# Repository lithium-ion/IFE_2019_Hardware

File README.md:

View this project on [CADLAB.io](https://cadlab.io/project/1221). 

# IFE_2019_Hardware
Hardware System - Eagle Files + Spice Code

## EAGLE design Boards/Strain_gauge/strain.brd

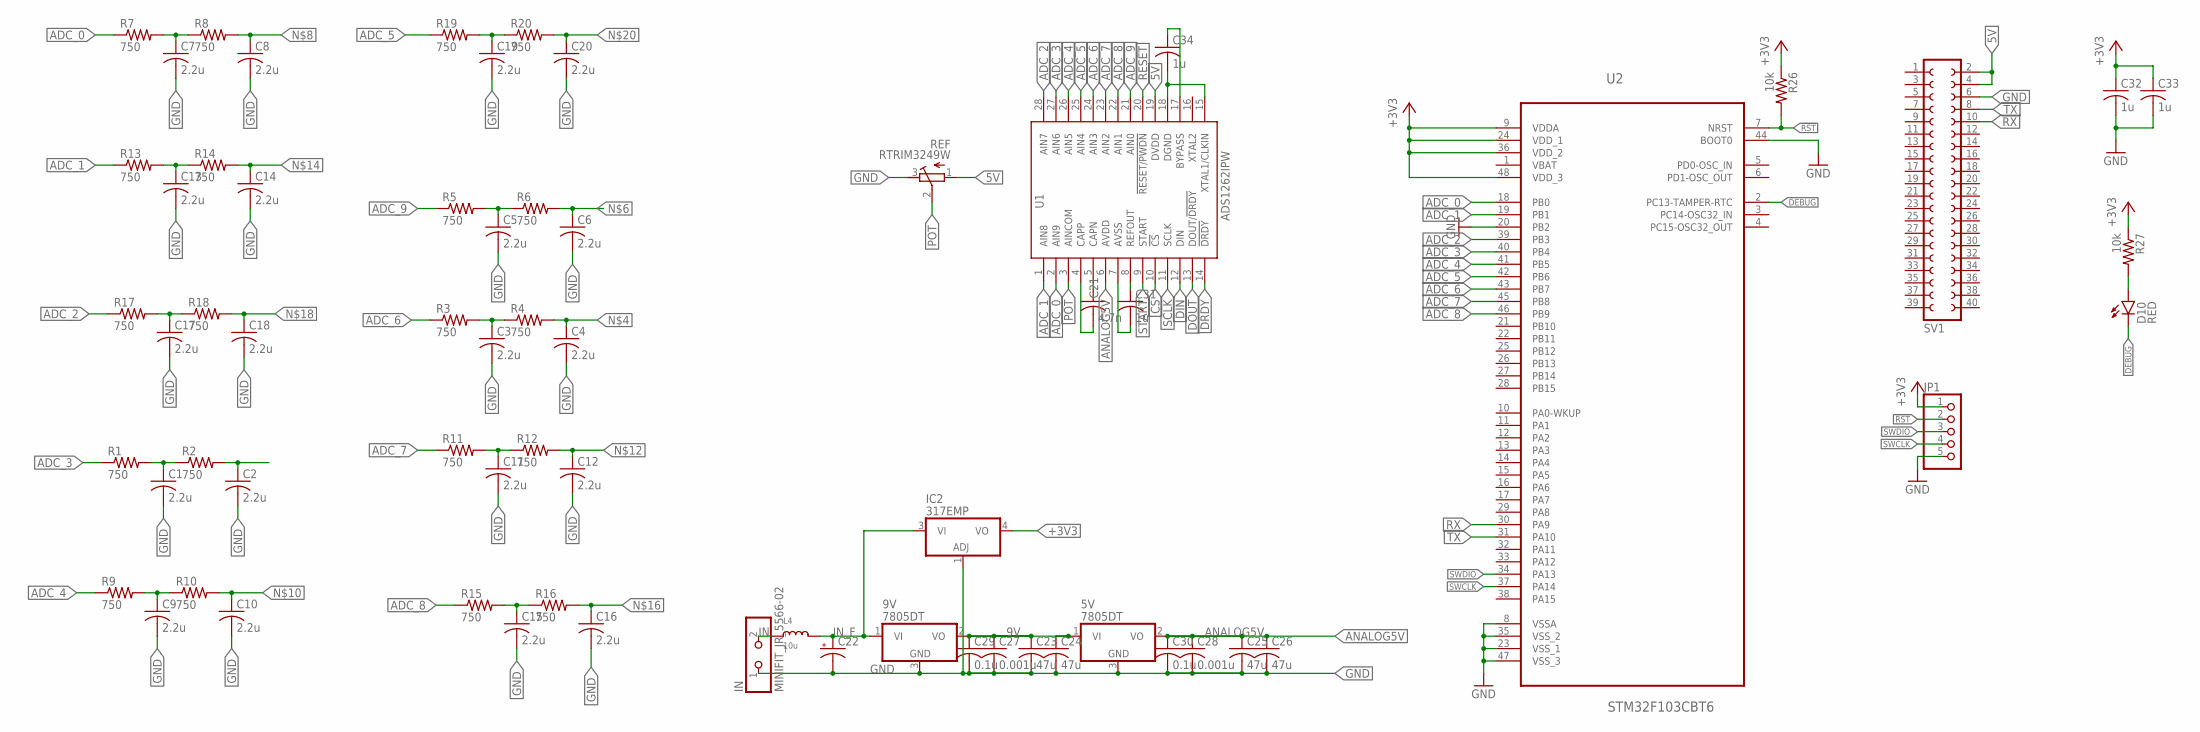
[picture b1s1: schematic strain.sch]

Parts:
5V, 9V: 7805DT; TO252
C1, C2, C3, C4, C5, C6, C7, C8, C9, C10, C11, C12, C13, C14, C15, C16, C17, C18, C19, C20: 2.2u; C0805
C21: 4.7n; C0805
C22: CPOL-USE5-10.5; E5-10,5
C23, C24, C25, C26: 47u; C1210
C27, C28: 0.001u; C0603
C29, C30: 0.1u; C0603
C31, C32, C33, C34: 1u; C0805
D10: RED; LED-0603
IC2: 317EMP; SOT223
IN: MINIFIT_JR_5566-02
JP1: PINHD-1X5; 1X05
L4: 10u; INDUCTOR_5X5MM_NR5040_NOTHERMALS
R1, R2, R3, R4, R5, R6, R7, R8, R9, R10, R11, R12, R13, R14, R15, R16, R17, R18, R19, R20: 750; R0805
R26, R27: 10k; R0603
REF: RTRIM3249W; RTRIM3299W
SV1: FE20-2
U1: ADS1262IPW; TSSOP28
U2: STM32F103CBT6; QFP50P900X900X160-48N

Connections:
5V: REF.1 (A), SV1.2, SV1.4, U1.19 (DVDD)
9V: 5V.1 (VI), 9V.2 (VO), C23.1, C24.1, C27.1, C29.1
!RST: JP1.2, R26.2, U2.7 (NRST)
+3V3: C32.1, C33.1, IC2.4 (VO), JP1.1, R26.1, R27.1, U2.9 (VDDA), U2.24 (VDD_1), U2.36 (VDD_2), U2.48 (VDD_3)
ADC_0: R7.1, U1.2 (AIN9), U2.18 (PB0)
ADC_1: R13.1, U1.1 (AIN8), U2.19 (PB1)
ADC_2: R17.1, U1.28 (AIN7), U2.39 (PB3)
ADC_3: R1.1, U1.27 (AIN6), U2.40 (PB4)
ADC_4: R9.1, U1.26 (AIN5), U2.41 (PB5)
ADC_5: R19.1, U1.25 (AIN4), U2.42 (PB6)
ADC_6: R3.1, U1.24 (AIN3), U2.43 (PB7)
ADC_7: R11.1, U1.23 (AIN2), U2.45 (PB8)
ADC_8: R15.1, U1.22 (AIN1), U2.46 (PB9)
ADC_9: R5.1, U1.21 (AIN0)
ANALOG5V: 5V.2 (VO), C25.1, C26.1, C28.1, C30.1, U1.6 (AVDD)
CS: U1.10 (!CS)
DEBUG: D10.C, U2.2 (PC13-TAMPER-RTC)
DGND: C34.2, U1.15 (XTAL1/CLKIN), U1.18 (DGND)
DIN: U1.12 (DIN)
DOUT: U1.13 (DOUT/!DRDY)
DRDY: U1.14 (!DRDY)
GND: 5V.3 (GND), 9V.3 (GND), C1.2, C2.2, C3.2, C4.2, C5.2, C6.2, C7.2, C8.2, C9.2, C10.2, C11.2, C12.2, C13.2, C14.2, C15.2, C16.2, C17.2, C18.2, C19.2, C20.2, C22.-, C23.2, C24.2, C25.2, C26.2, C27.2, C28.2, C29.2, C30.2, C32.2, C33.2, IC2.1 (ADJ), IN.1, JP1.5, REF.3 (E), SV1.6, U2.8 (VSSA), U2.20 (PB2), U2.23 (VSS_1), U2.35 (VSS_2), U2.44 (BOOT0), U2.47 (VSS_3)
IN: IN.2, L4.P$1 (1)
IN_F: 9V.1 (VI), C22.+, IC2.3 (VI), L4.P$2 (2)
unnamed: C1.1, R1.2, R2.1
unnamed: C2.1, R2.2
unnamed: C3.1, R3.2, R4.1
unnamed: C4.1, R4.2
unnamed: C5.1, R5.2, R6.1
unnamed: C6.1, R6.2
unnamed: C7.1, R7.2, R8.1
unnamed: C8.1, R8.2
unnamed: C9.1, R9.2, R10.1
unnamed: C10.1, R10.2
unnamed: C11.1, R11.2, R12.1
unnamed: C12.1, R12.2
unnamed: C13.1, R13.2, R14.1
unnamed: C14.1, R14.2
unnamed: C15.1, R15.2, R16.1
unnamed: C16.1, R16.2
unnamed: C17.1, R17.2, R18.1
unnamed: C18.1, R18.2
unnamed: C19.1, R19.2, R20.1
unnamed: C20.1, R20.2
unnamed: D10.A, R27.2
unnamed: C21.1, C21.2, U1.4 (CAPP), U1.5 (CAPN)
unnamed: C31.1, U1.8 (REFOUT)
unnamed: C31.2, U1.7 (AVSS)
unnamed: C34.1, U1.17 (BYPASS)
PA11: U2.32 (PA11)
POT: REF.2 (S), U1.3 (AINCOM)
RESET: U1.20 (!RESET/PWDN)
RX: SV1.10, U2.30 (PA9)
SCLK: U1.11 (SCLK)
START: U1.9 (START)
SWCLK: JP1.4, U2.37 (PA14)
SWDIO: JP1.3, U2.34 (PA13)
TX: SV1.8, U2.31 (PA10)

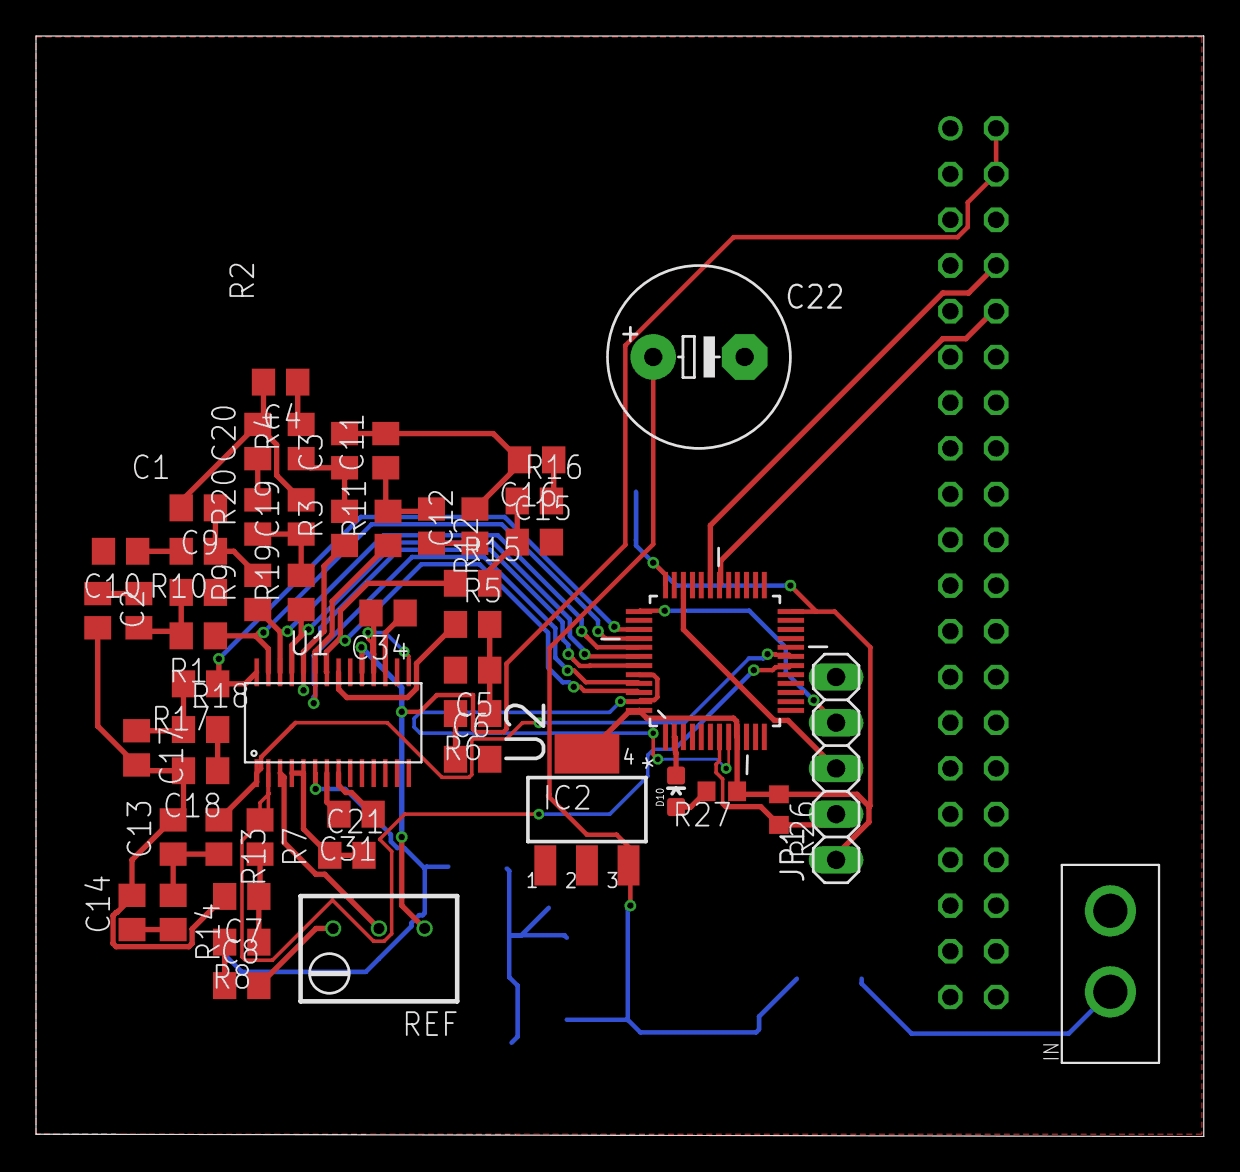
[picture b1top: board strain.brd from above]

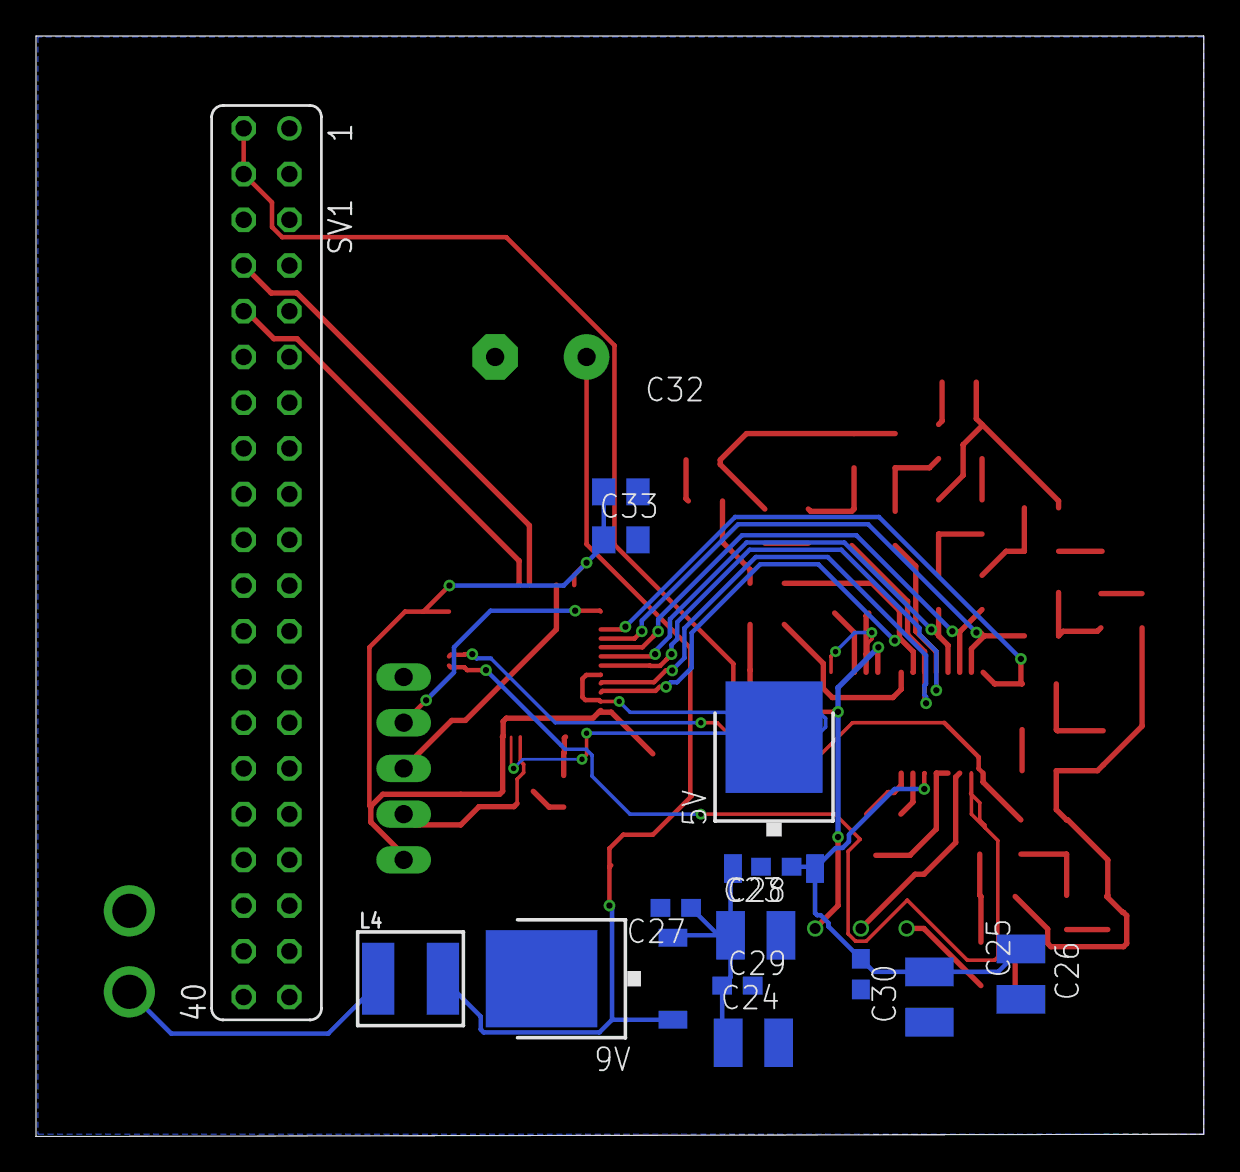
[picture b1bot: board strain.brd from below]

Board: 2 copper layers, 64.9 x 61.1 mm, 67 parts (14 on the bottom side), 50 nets.

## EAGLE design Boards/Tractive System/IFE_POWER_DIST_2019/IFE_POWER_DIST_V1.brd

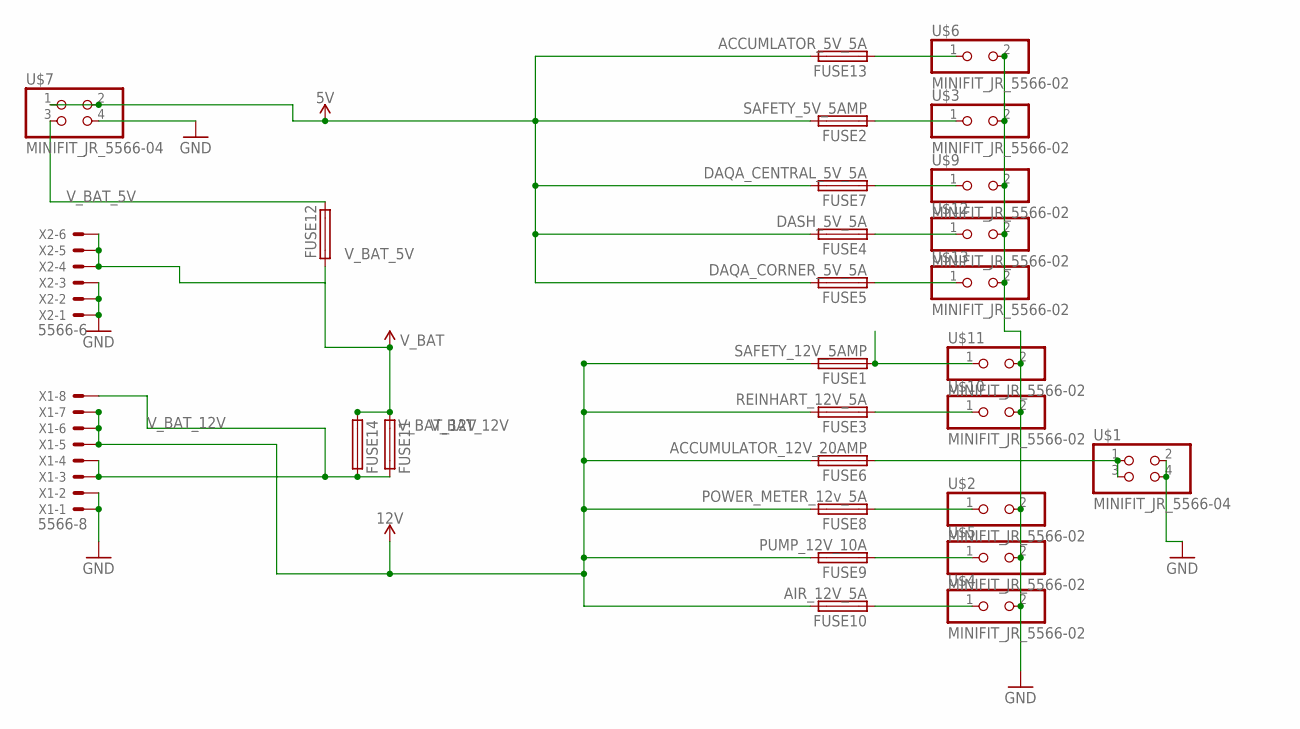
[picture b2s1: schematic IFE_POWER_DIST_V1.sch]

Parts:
FUSE1: SAFETY_12V_5AMP; 3568
FUSE2: SAFETY_5V_5AMP; 3568
FUSE3: REINHART_12V_5A; 3568
FUSE4: DASH_5V_5A; 3568
FUSE5: DAQA_CORNER_5V_5A; 3568
FUSE6: ACCUMULATOR_12V_20AMP; 3568
FUSE7: DAQA_CENTRAL_5V_5A; 3568
FUSE8: POWER_METER_12v_5A; 3568
FUSE9: PUMP_12V_10A; 3568
FUSE10: AIR_12V_5A; 3568
FUSE11, FUSE14: V_BAT_12V; 3568
FUSE12: V_BAT_5V; 3568
FUSE13: ACCUMLATOR_5V_5A; 3568
U$1, U$7: MINIFIT_JR_5566-04
U$2, U$3, U$4, U$5, U$6, U$9, U$10, U$11, U$12, U$13: MINIFIT_JR_5566-02
X1: 5566-8
X2: 5566-6

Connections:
5V: FUSE2.P$2 (2), FUSE2.P$3 (2), FUSE4.P$2 (2), FUSE4.P$3 (2), FUSE5.P$2 (2), FUSE5.P$3 (2), FUSE7.P$2 (2), FUSE7.P$3 (2), FUSE13.P$2 (2), FUSE13.P$3 (2), U$7.1, U$7.2
12V: FUSE1.P$2 (2), FUSE1.P$3 (2), FUSE3.P$2 (2), FUSE3.P$3 (2), FUSE6.P$2 (2), FUSE6.P$3 (2), FUSE8.P$2 (2), FUSE8.P$3 (2), FUSE9.P$2 (2), FUSE9.P$3 (2), FUSE10.P$2 (2), FUSE10.P$3 (2), X1.5, X1.6, X1.7
GND: U$1.2, U$1.4, U$2.2, U$3.2, U$4.2, U$5.2, U$6.2, U$7.4, U$9.2, U$10.2, U$11.2, U$12.2, U$13.2, X1.1, X1.2, X2.1, X2.2, X2.3
unnamed: FUSE5.P$1 (1), FUSE5.P$4 (1), U$13.1
unnamed: FUSE7.P$1 (1), FUSE7.P$4 (1), U$9.1
unnamed: FUSE4.P$1 (1), FUSE4.P$4 (1), U$12.1
unnamed: FUSE2.P$1 (1), FUSE2.P$4 (1), U$3.1
unnamed: FUSE10.P$1 (1), FUSE10.P$4 (1), U$4.1
unnamed: FUSE1.P$1 (1), FUSE1.P$4 (1), U$11.1
unnamed: FUSE3.P$1 (1), FUSE3.P$4 (1), U$10.1
unnamed: FUSE8.P$1 (1), FUSE8.P$4 (1), U$2.1
unnamed: FUSE9.P$1 (1), FUSE9.P$4 (1), U$5.1
unnamed: FUSE6.P$1 (1), FUSE6.P$4 (1), U$1.1, U$1.3
unnamed: FUSE13.P$1 (1), FUSE13.P$4 (1), U$6.1
VCC: FUSE11.P$1 (1), FUSE11.P$4 (1), FUSE12.P$1 (1), FUSE12.P$4 (1), FUSE14.P$1 (1), FUSE14.P$4 (1), X2.4, X2.5, X2.6
V_BAT_5V: FUSE12.P$2 (2), FUSE12.P$3 (2), U$7.3
V_BAT_12V: FUSE11.P$2 (2), FUSE11.P$3 (2), FUSE14.P$2 (2), FUSE14.P$3 (2), X1.3, X1.4, X1.8

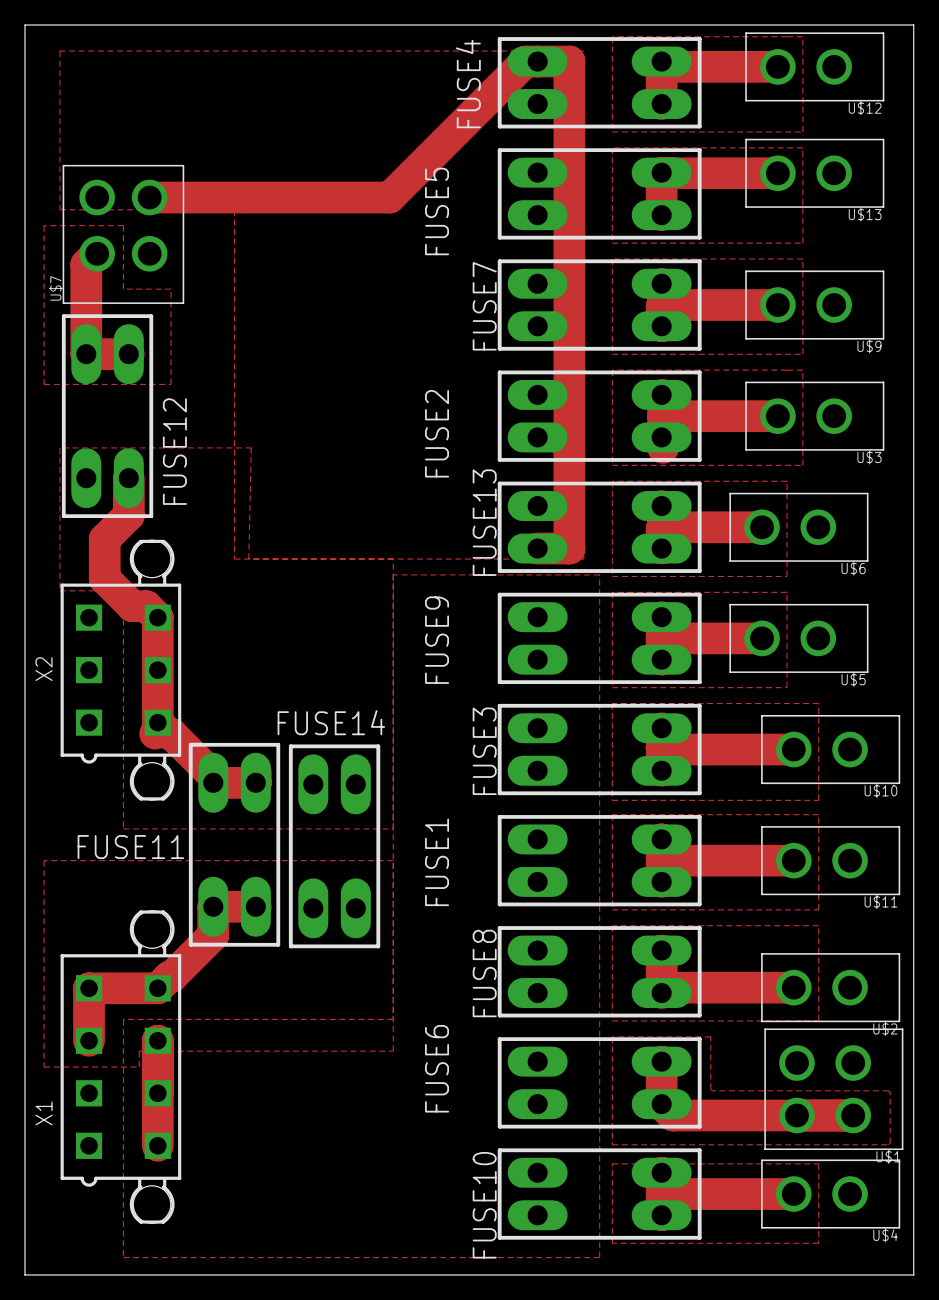
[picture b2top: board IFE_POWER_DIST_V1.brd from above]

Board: 2 copper layers, 71.1 x 100.0 mm, 28 parts (0 on the bottom side), 17 nets.

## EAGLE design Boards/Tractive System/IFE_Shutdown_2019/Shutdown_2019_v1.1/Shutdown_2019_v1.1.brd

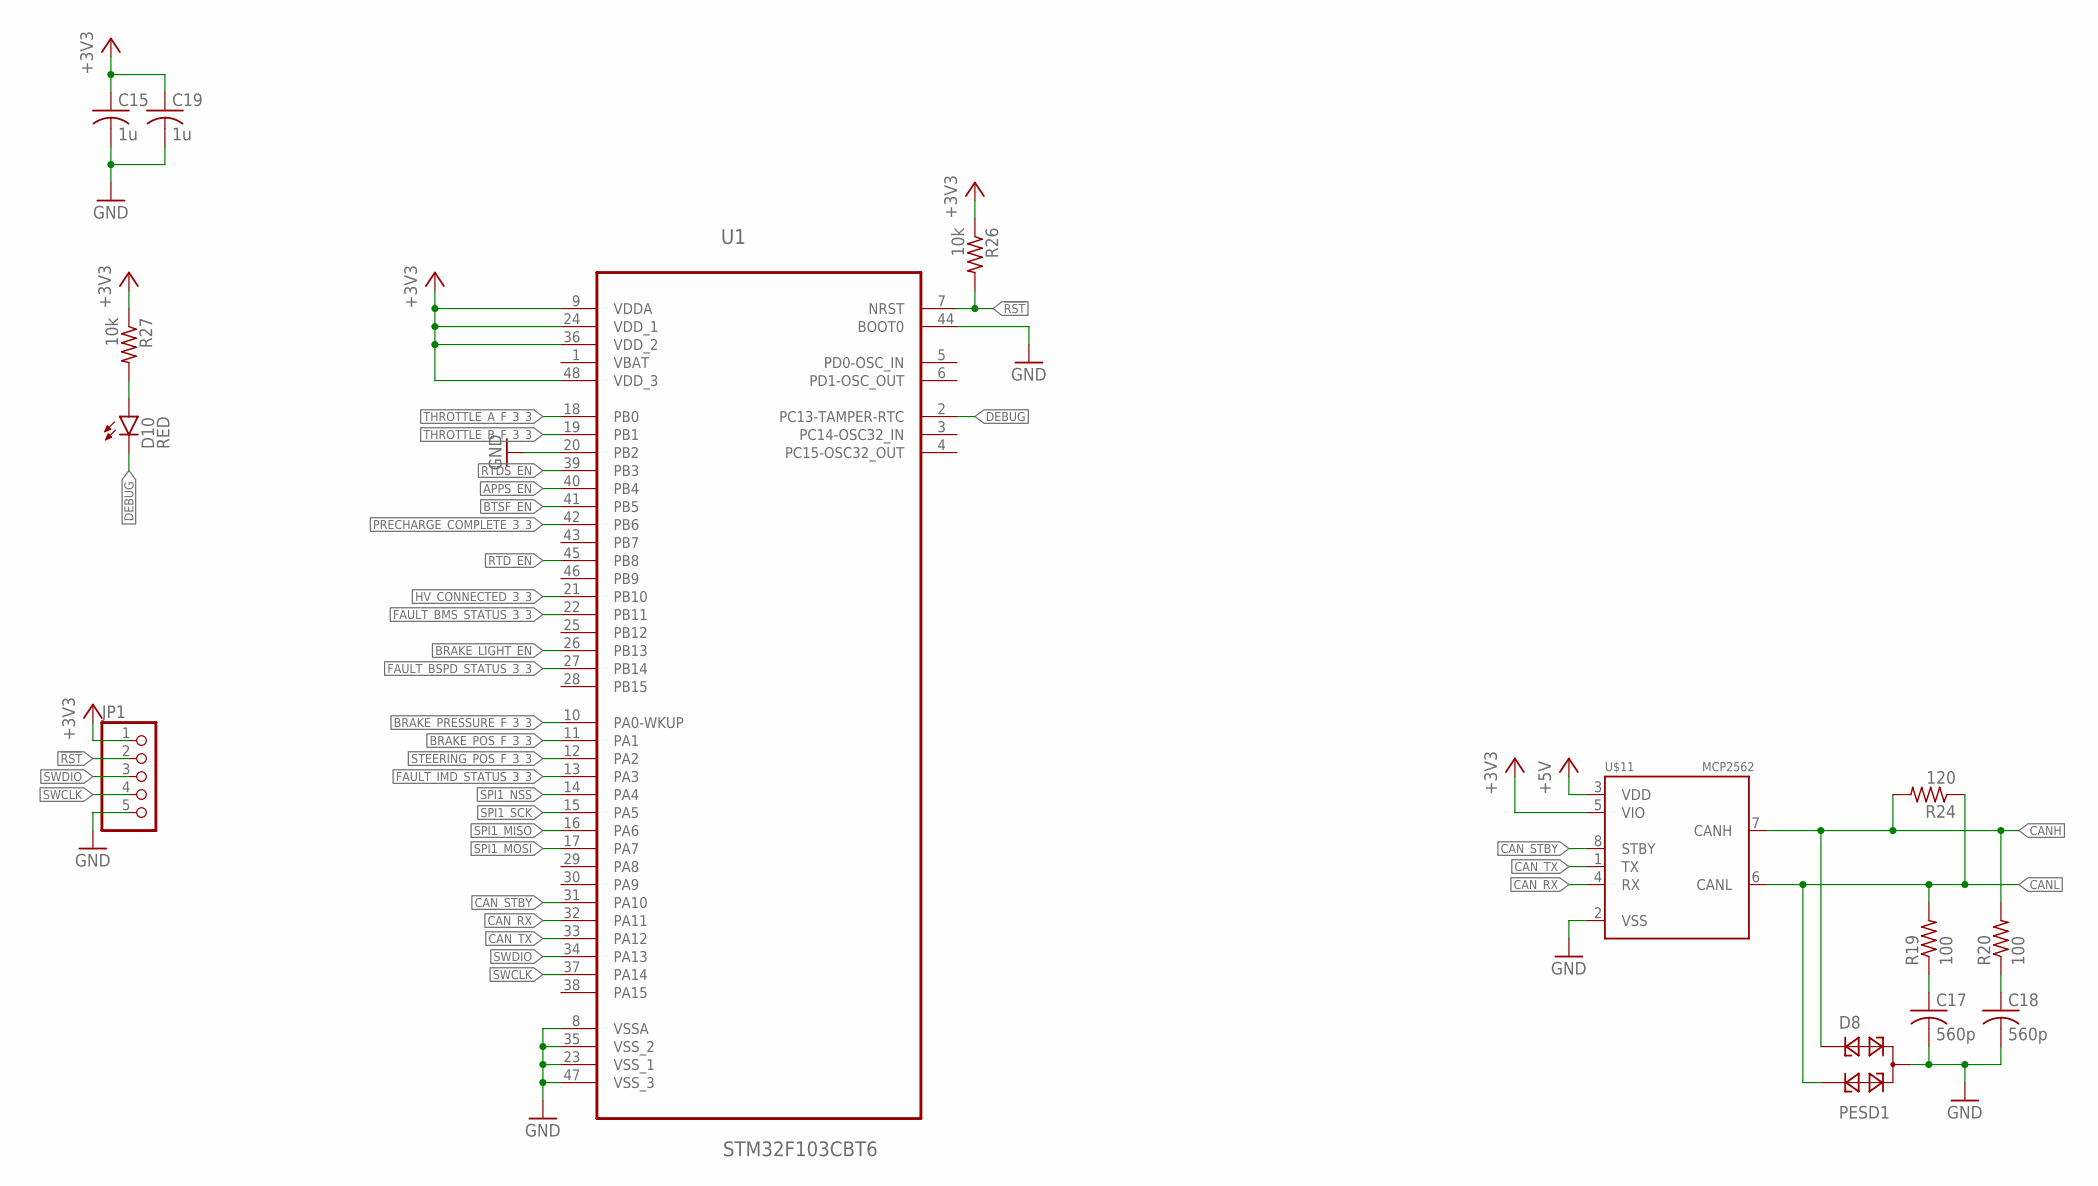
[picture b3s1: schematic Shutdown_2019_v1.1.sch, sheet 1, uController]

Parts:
C15, C19: 1u; C0805
C17, C18: 560p; C0603
D8: PESD1; SOT23
D10: RED; LED-0603
JP1: PINHD-1X5; 1X05
R19, R20: 100; R0603
R24: 120; R0603
R26, R27: 10k; R0603
U1: STM32F103CBT6; QFP50P900X900X160-48N
U$11: MCP2562; SOIC8

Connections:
!RST: JP1.2, R26.2, U1.7 (NRST)
+3V3: C15.1, C19.1, JP1.1, R26.1, R27.1, U1.9 (VDDA), U1.24 (VDD_1), U1.36 (VDD_2), U1.48 (VDD_3), U$11.5 (VIO); also elsewhere on the board
+5V: U$11.3 (VDD); also elsewhere on the board
APPS_EN: U1.40 (PB4); also elsewhere on the board
BRAKE_LIGHT_EN: U1.26 (PB13); also elsewhere on the board
BRAKE_POS_F_3_3: U1.11 (PA1); also elsewhere on the board
BRAKE_PRESSURE_F_3_3: U1.10 (PA0-WKUP); also elsewhere on the board
BTSF_EN: U1.41 (PB5); also elsewhere on the board
CANH: D8.1, R20.2, R24.2, U$11.7 (CANH); also elsewhere on the board
CANL: D8.2, R19.2, R24.1, U$11.6 (CANL); also elsewhere on the board
CAN_RX: U1.32 (PA11), U$11.4 (RX)
CAN_STBY: U1.31 (PA10), U$11.8 (STBY)
CAN_TX: U1.33 (PA12), U$11.1 (TX)
DEBUG: D10.C, U1.2 (PC13-TAMPER-RTC)
FAULT_BMS_STATUS_3_3: U1.22 (PB11); also elsewhere on the board
FAULT_BSPD_STATUS_3_3: U1.27 (PB14); also elsewhere on the board
FAULT_IMD_STATUS_3_3: U1.13 (PA3); also elsewhere on the board
GND: C15.2, C17.2, C18.2, C19.2, D8.3, JP1.5, U1.8 (VSSA), U1.20 (PB2), U1.23 (VSS_1), U1.35 (VSS_2), U1.44 (BOOT0), U1.47 (VSS_3), U$11.2 (VSS); also elsewhere on the board
HV_CONNECTED_3_3: U1.21 (PB10); also elsewhere on the board
unnamed: C17.1, R19.1
unnamed: C18.1, R20.1
unnamed: D10.A, R27.2
PRECHARGE_COMPLETE_3_3: U1.42 (PB6); also elsewhere on the board
RTDS_EN: U1.39 (PB3); also elsewhere on the board
RTD_EN: U1.45 (PB8); also elsewhere on the board
SPI1_MISO: U1.16 (PA6); also elsewhere on the board
SPI1_MOSI: U1.17 (PA7); also elsewhere on the board
SPI1_NSS: U1.14 (PA4); also elsewhere on the board
SPI1_SCK: U1.15 (PA5); also elsewhere on the board
STEERING_POS_F_3_3: U1.12 (PA2); also elsewhere on the board
SWCLK: JP1.4, U1.37 (PA14)
SWDIO: JP1.3, U1.34 (PA13)
THROTTLE_A_F_3_3: U1.18 (PB0); also elsewhere on the board
THROTTLE_B_F_3_3: U1.19 (PB1); also elsewhere on the board

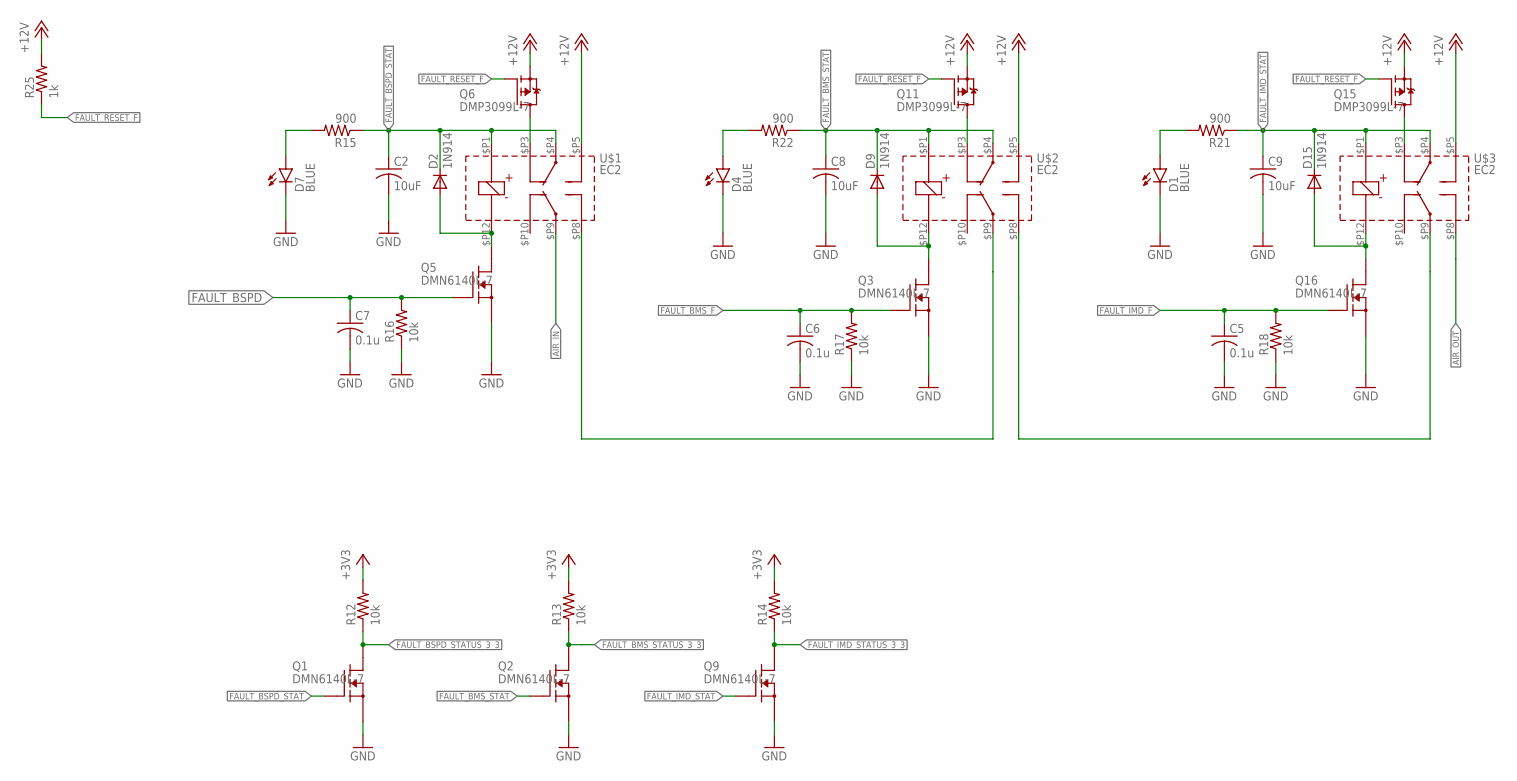
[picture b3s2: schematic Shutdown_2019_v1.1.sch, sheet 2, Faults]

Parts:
C2, C8, C9: 10uF; C0805
C5, C6, C7: 0.1u; C0603
D1, D4, D7: BLUE; LED-0603
D2, D9, D15: 1N914; SOD323-F
Q1, Q2, Q3, Q5, Q9, Q16: DMN6140L-7; SOT23
Q6, Q11, Q15: DMP3099L-7; SOT23
R12, R13, R14, R16, R17, R18: 10k; R0603
R15, R21, R22: 900; R0603
R25: 1k; R0603
U$1, U$2, U$3: EC2; DPDT_2.54

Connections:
+3V3: R12.2, R13.2, R14.2; also elsewhere on the board
+12V: Q6.2 (S), Q11.2 (S), Q15.2 (S), R25.2, U$1.$P5, U$2.$P5, U$3.$P5; also elsewhere on the board
AIR_IN: U$1.$P9; also elsewhere on the board
AIR_OUT: U$3.$P8; also elsewhere on the board
FAULT_BMS_F: C6.1, Q3.1 (G), R17.2; also elsewhere on the board
FAULT_BMS_STAT: C8.1, D9.C, Q2.1 (G), R22.1, U$2.$P1, U$2.$P4; also elsewhere on the board
FAULT_BMS_STATUS_3_3: Q2.3 (D), R13.1; also elsewhere on the board
FAULT_BSPD: C7.1, Q5.1 (G), R16.2; also elsewhere on the board
FAULT_BSPD_STAT: C2.1, D2.C, Q1.1 (G), R15.1, U$1.$P1, U$1.$P4; also elsewhere on the board
FAULT_BSPD_STATUS_3_3: Q1.3 (D), R12.1; also elsewhere on the board
FAULT_IMD_F: C5.1, Q16.1 (G), R18.2; also elsewhere on the board
FAULT_IMD_STAT: C9.1, D15.C, Q9.1 (G), R21.1, U$3.$P1, U$3.$P4; also elsewhere on the board
FAULT_IMD_STATUS_3_3: Q9.3 (D), R14.1; also elsewhere on the board
FAULT_RESET_F: Q6.1 (G), Q11.1 (G), Q15.1 (G), R25.1; also elsewhere on the board
GND: C2.2, C5.2, C6.2, C7.2, C8.2, C9.2, D1.C, D4.C, D7.C, Q1.2 (S), Q2.2 (S), Q3.2 (S), Q5.2 (S), Q9.2 (S), Q16.2 (S), R16.1, R17.1, R18.1; also elsewhere on the board
unnamed: D9.A, Q3.3 (D), U$2.$P12
unnamed: D7.A, R15.2
unnamed: U$1.$P8, U$2.$P9
unnamed: Q6.3 (D), U$1.$P3
unnamed: U$2.$P8, U$3.$P9
unnamed: D2.A, Q5.3 (D), U$1.$P12
unnamed: D4.A, R22.2
unnamed: Q11.3 (D), U$2.$P3
unnamed: D1.A, R21.2
unnamed: Q15.3 (D), U$3.$P3
unnamed: D15.A, Q16.3 (D), U$3.$P12

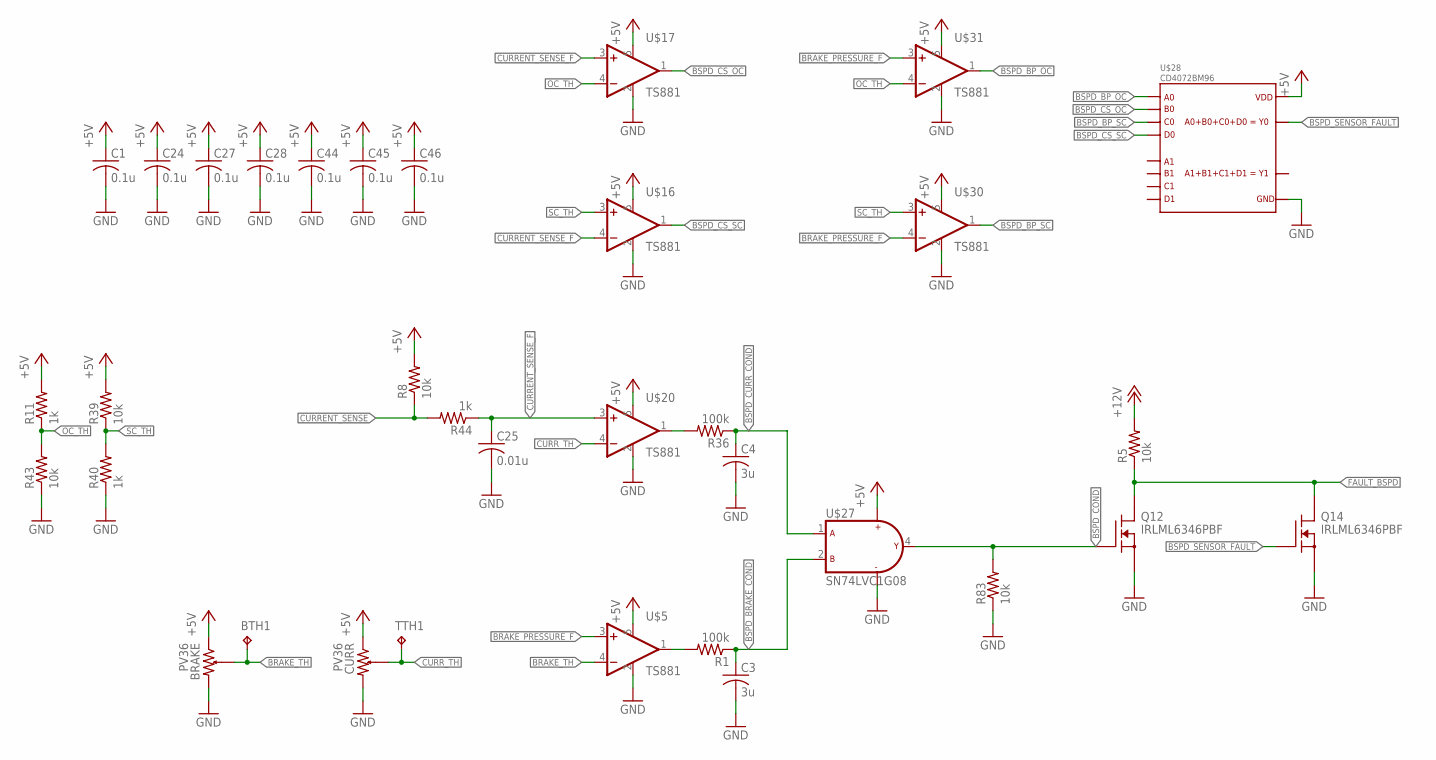
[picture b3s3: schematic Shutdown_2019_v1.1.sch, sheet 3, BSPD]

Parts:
BRAKE: PV36
BTH1: TPTP09R; TP09R
C1, C24, C27, C28, C44, C45, C46: 0.1u; C0603
C3, C4: 3u; C0603
C25: 0.01u; C0603
CURR: PV36
Q12, Q14: IRLML6346PBF; SOT23
R1, R36: 100k; R0603
R5, R8, R39, R43, R83: 10k; R0603
R11, R40, R44: 1k; R0603
TTH1: TPTP09R; TP09R
U$5, U$16, U$17, U$20, U$30, U$31: TS881; SOT23-5
U$27: SN74LVC1G08; SOT23-5
U$28: CD4072BM96; SOIC8

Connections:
+5V: BRAKE.A, C1.1, C24.1, C27.1, C28.1, C44.1, C45.1, C46.1, CURR.A, R8.2, R11.2, R39.2, U$5.5 (VDD), U$16.5 (VDD), U$17.5 (VDD), U$20.5 (VDD), U$27.5 (VDD), U$28.P14 (VDD), U$30.5 (VDD), U$31.5 (VDD); also elsewhere on the board
+12V: R5.2; also elsewhere on the board
BRAKE_PRESSURE_F: U$5.3 (+IN), U$30.4 (-IN), U$31.3 (+IN); also elsewhere on the board
BRAKE_TH: BRAKE.W, BTH1.TP, U$5.4 (-IN)
BSPD_BP_OC: U$28.P2 (A0), U$31.1 (OUT)
BSPD_BP_SC: U$28.P4 (C0), U$30.1 (OUT)
BSPD_BRAKE_COND: C3.1, R1.1, U$27.2 (B)
BSPD_COND: Q12.1 (G), R83.2, U$27.4 (Y)
BSPD_CS_OC: U$17.1 (OUT), U$28.P3 (B0)
BSPD_CS_SC: U$16.1 (OUT), U$28.P5 (D0)
BSPD_CURR_COND: C4.1, R36.1, U$27.1 (A)
BSPD_SENSOR_FAULT: Q14.1 (G), U$28.P1 (Y0)
CURRENT_SENSE: R8.1, R44.2; also elsewhere on the board
CURRENT_SENSE_F: C25.1, R44.1, U$16.4 (-IN), U$17.3 (+IN), U$20.3 (+IN)
CURR_TH: CURR.W, TTH1.TP, U$20.4 (-IN)
FAULT_BSPD: Q12.3 (D), Q14.3 (D), R5.1; also elsewhere on the board
GND: BRAKE.B, C1.2, C3.2, C4.2, C24.2, C25.2, C27.2, C28.2, C44.2, C45.2, C46.2, CURR.B, Q12.2 (S), Q14.2 (S), R40.1, R43.1, R83.1, U$5.2 (GND), U$16.2 (GND), U$17.2 (GND), U$20.2 (GND), U$27.3 (GND), U$28.P7 (GND), U$30.2 (GND), U$31.2 (GND); also elsewhere on the board
unnamed: R36.2, U$20.1 (OUT)
unnamed: R1.2, U$5.1 (OUT)
OC_TH: R11.1, R43.2, U$17.4 (-IN), U$31.4 (-IN)
SC_TH: R39.1, R40.2, U$16.3 (+IN), U$30.3 (+IN)

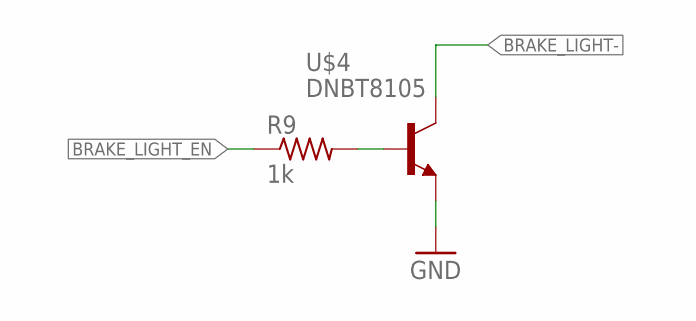
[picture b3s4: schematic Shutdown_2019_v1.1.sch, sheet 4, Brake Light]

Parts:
R9: 1k; R0603
U$4: DNBT8105; SOT23-3

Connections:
BRAKE_LIGHT-: U$4.3 (C); also elsewhere on the board
BRAKE_LIGHT_EN: R9.1; also elsewhere on the board
GND: U$4.2 (E); also elsewhere on the board
unnamed: R9.2, U$4.1 (B)

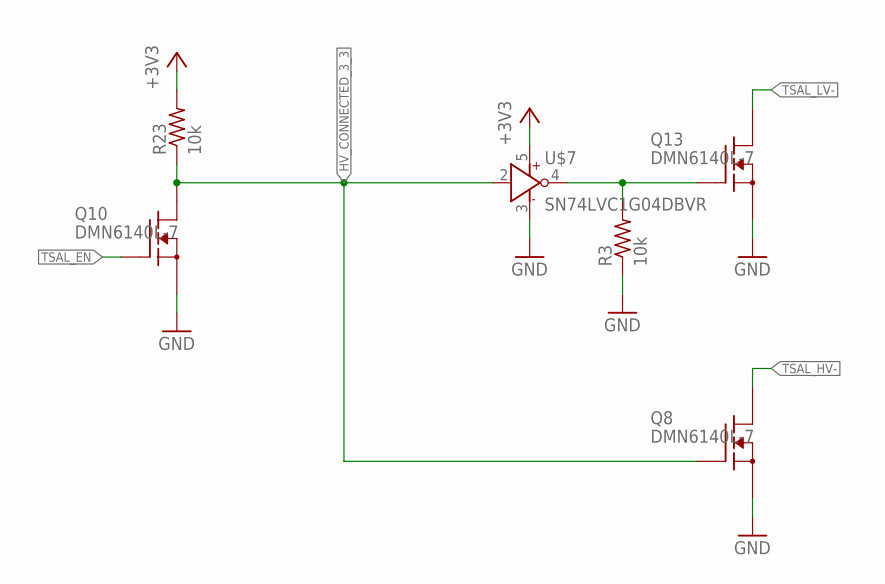
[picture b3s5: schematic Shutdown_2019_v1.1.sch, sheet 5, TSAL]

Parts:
Q8, Q10, Q13: DMN6140L-7; SOT23
R3, R23: 10k; R0603
U$7: SN74LVC1G04DBVR; SOT23-5L

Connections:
+3V3: R23.2, U$7.5 (V+); also elsewhere on the board
GND: Q8.2 (S), Q10.2 (S), Q13.2 (S), R3.1, U$7.3 (GND); also elsewhere on the board
HV_CONNECTED_3_3: Q8.1 (G), Q10.3 (D), R23.1, U$7.2 (A); also elsewhere on the board
unnamed: Q13.1 (G), R3.2, U$7.4 (Y)
TSAL_EN: Q10.1 (G); also elsewhere on the board
TSAL_HV-: Q8.3 (D); also elsewhere on the board
TSAL_LV-: Q13.3 (D); also elsewhere on the board

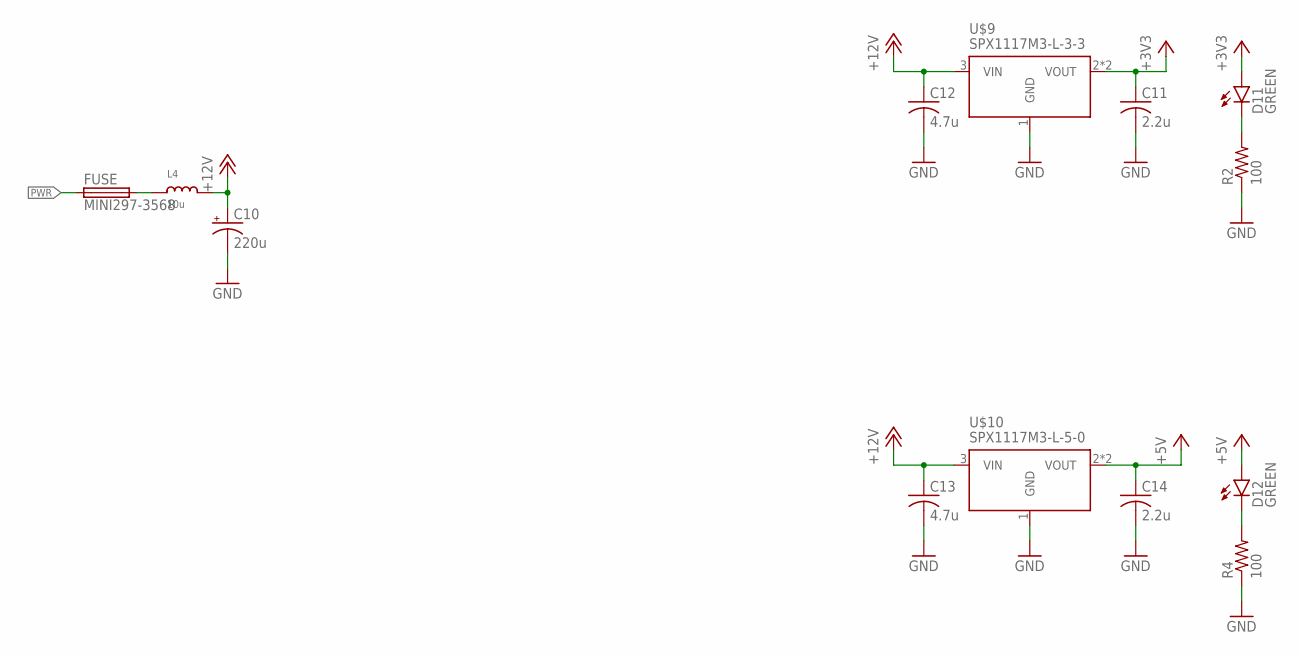
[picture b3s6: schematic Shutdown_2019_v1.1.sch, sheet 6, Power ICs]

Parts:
C10: 220u; E2,5-7
C11, C14: 2.2u; C0805
C12, C13: 4.7u; C0805
D11, D12: GREEN; LED-0603
FUSE: MINI297-3568; 3568
L4: 10u; INDUCTOR_5X5MM_NR5040_NOTHERMALS
R2, R4: 100; R0603
U$9: SPX1117M3-L-3-3; SOT223
U$10: SPX1117M3-L-5-0; SOT223

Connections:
+3V3: C11.1, D11.A, U$9.2 (VOUT), U$9.4 (VOUT); also elsewhere on the board
+5V: C14.1, D12.A, U$10.2 (VOUT), U$10.4 (VOUT); also elsewhere on the board
+12V: C10.+, C12.1, C13.1, L4.P$2 (2), U$9.3 (VIN), U$10.3 (VIN); also elsewhere on the board
GND: C10.-, C11.2, C12.2, C13.2, C14.2, R2.1, R4.1, U$9.1 (GND), U$10.1 (GND); also elsewhere on the board
unnamed: FUSE.P$2 (2), FUSE.P$3 (2), L4.P$1 (1)
unnamed: D12.C, R4.2
unnamed: D11.C, R2.2
PWR: FUSE.P$1 (1), FUSE.P$4 (1); also elsewhere on the board

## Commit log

2018-06-27 Precharge M2019 Simulation Development
2018-07-01 Adjusted relay model
2018-07-18 Backlink to CADLAB.io has been added.
2018-07-18 Created Parts Library Folder
    Created a Library Folder and added some basic libraries to it. Will add more libraries and update
2018-07-18 Created proper folder structure for boards
    Moved precharge folder into sub directory
2018-07-18 Added Design blocks
2018-07-18 Added DRC, CAM and Logos
2018-07-18 Added BMS_Slave to repo
2018-07-18 Added old revision of BMS_Slave
2018-07-19 Added Parts list for BMS
2018-07-19 Removed Parts list
2018-07-19 Adding Precharge Progress
2018-07-19 Adding git ignore
2018-07-19 Removing temp files
2018-07-20 Why isnt the gitignore working?! also updated precharge to clean it up a bit
2018-07-20 More precharge organization
2018-07-30 Adjusted precharge relay package, reduced area
2018-07-31 More shutdown work
2018-08-01 Adding circuitry to shutdown, relay drivers
2018-08-01 Added experimental BMS balance circuit spice models
2018-08-02 Safety board cleanup
2018-08-03 Working on Power Supply and Light Drivers for Safety Board
2018-08-06 Finishing power distribution on safety board
2018-08-07 added CAN circuit and DEBUG headder
2018-08-10 Adding Spice Model for BSPD
2018-08-13 Added digital POT for TC
2018-08-13 starting to connect subsystems
2018-08-14 Added traction control mucrocontroller
2018-09-17 Rework Enable
2018-09-18 created op amp buffer
2018-09-19 More work, inputs protected with zener and LPF
2018-09-22 Nearly complete... Just BSPD Circuit left
2018-09-22 Moving to layout of shutdown
2018-09-22 Beginning initial Safety route
2018-09-22 nearly done with routing
2018-09-22 Done with safety initial layout
2018-09-23 Added rounded edges + Silk
2018-09-28 adding dash to the repository
2018-10-25 new dash revisions
2018-11-03 fixing precharge + Shutdown
2018-11-03 Updating safetyV1.1
2018-11-04 Still working on 1.1
2018-11-04 Finished pre review Safety V1.1
2018-11-07 dash v_2 cleanup
2018-11-07 more tweaks
2018-11-07 more routing
2018-11-08 v2 done
2018-11-09 final revisions for 2
2018-11-10 adding the zip folder for vs
2018-11-10 Added TSAL Board
2018-12-02 Ready to route
2018-12-02 finished safety v1.1 layout
2018-12-02 Precharge 1.2 finished, added .gitignore
2018-12-03 added BMS files from sharepoint
2018-12-03 power dist ish
2018-12-03 BMSMaster completed
2018-12-03 Power dist final edits
2018-12-03 Getting rid of the unessicary files, it fucks up
2018-12-03 # fucks up merges
2018-12-03 fucked up the merge
2018-12-03 fucks up merge
2018-12-03 fuse replacement
2018-12-04 Powerdist with working CAM
2018-12-04 Removed all stupid files
2018-12-08 Schematic finished for strain gauges, going to work on board when I wake up
2018-12-08 updated testing sch
2018-12-10 Rushed the fuck out of the ADS1262 board, but here it is
2018-12-13 Added the full BMS Slave board
2018-12-24 Output files for v1-full BMS
2018-12-24 Output images for v1-full BMS
2018-12-25 Create IFE_2019_TSAL_Discharge
2019-01-04 BMS Slave v2 board complete
2019-01-05 BMS Slave cleaned up and Master created
2019-01-06 TSAL_Discharge_TSMP and AIL added
2019-01-08 AIL added mounting holes and put LED and bottom
2019-01-10 More work done on BMS Master
2019-01-10 adding altium version of shutdown
2019-01-10 adding altium vresion of precharge
2019-01-14 Lots of cleanup and added amplifier to BMS Master
2019-01-14 More cleanup of stuff for the ESF
2019-01-22 BMS Master updates, will be ready to order in next commit
2019-02-05 Added pedal board intial trial
2019-02-11 Added charger board and some other minor changes
2019-02-11 Added a bunch more stuff to various boards overnight
2019-02-12 Pushing the TSAL Light
2019-02-12 adding altium schematic
2019-02-12 finished TSAL BITCH
2019-02-12 finished TSAL BITCH for real for real
2019-02-12 Minor updates to the Slave board
2019-02-12 Gerber files of the TSAL Light generated
2019-02-13 this should be up to date but just checking
2019-02-13 should be done
2019-02-14 need to name some comps and do the TC sheet
2019-02-15 transfered over, just needs a few touches
2019-02-19 More completed Pedal board
2019-02-19 Started brake pedal board for MattZ
2019-03-01 Updated Pedal board with DXF and started LTC6811 BMS
2019-03-03 LTC6811 and SPICE Sim
2019-03-04 Completed LTC6811 Slave and made AIL smaller
    Will update AIL later with chnages based on DXF from Matt
2019-03-05 commitimg safety real quick
2019-03-05 Updated .gitignore to include a 250MB file that can't be pushed to git
2019-03-05 Updated DRC and board outline of safety board
2019-03-06 random drc errors
2019-03-06 Charger and HV board updated
2019-03-06 Updated Charger with Pads instead of Vias so that STEP export worked right
2019-03-06 AIL updated
2019-03-12 Created BMS Master with STM32F4
2019-03-16 pushing safety
2019-03-22 AIL and new SPICE Sims
2019-03-22 Need to route traces
2019-03-22 added schematic and pcb
2019-03-23 Minor cosmetic changes to BMS Master and PD Board
2019-03-23 Moved things around on PD
2019-03-23 Preliminary traces routed
2019-03-23 Updated PDB with new rules
2019-03-23 fook
2019-03-23 Routed PDB
2019-03-24 Changed some text and 3d model for MF_8
2019-03-24 Generated a bunch of Gerbers and STEP files
2019-03-24 Lots of updates to lots of boards
2019-03-25 finished drc, gonna re add ground planes
2019-03-25 gnd and drc
2019-03-25 small save
2019-03-25 safety board
2019-03-25 Pedals, BMS Master schematic, BMS Slave and a few other things
2019-03-25 forgot to save whoops
2019-03-25 Updated Dash
2019-03-25 Updated Safety Layout with TH testpoints
2019-03-25 fixes made
2019-03-25 fixed dash
2019-03-25 added bom
2019-03-25 forgot to save
2019-03-25 bom in output files folder
2019-03-25 safety gerbers generated, dash needs connector replaced
2019-03-25 smol fixes
2019-03-25 Fixed Dash component placement
2019-03-25 w holes
2019-03-26 Dash layout completed and gerbers generated
2019-04-01 mounting holes and power points and realignment
2019-04-01 should be ready for review
2019-04-01 BMS Slave v2 completed and all output files generated
2019-04-03 Generated gerbers and made final changes to Master, AIL, Slave and Dash for hopefully the last order
2019-04-08 Updated some schematics for ESF
2019-04-10 final rev hopefully
2019-04-10 solder mask
2019-04-10 realigned pins
2019-04-10 changed to commmon anode
2019-04-10 test stuff
2019-04-11 added the zener filter
2019-04-15 push before old checkout
2019-04-15 push before adding old
2019-04-15 adding older revision
2019-04-15 Removed random large files
2019-04-18 Dash manufacturing files created
2019-04-18 updated layout
2019-04-18 Safety completed and gerbers generted
2019-04-24 BMS Test board generated
2019-05-09 BMS SLave test carrier board
2019-06-02 Bunch of BMS Master and Slave revisions as a last ditch effort
2019-06-10 Dual BMS Master completed
2019-07-12 document on safety

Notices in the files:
parts and their libraries:
SparkFun-LED: Licensing: Creative Commons ShareAlike 4.0 International - https://creativecommons.org/licenses/by-sa/4.0
